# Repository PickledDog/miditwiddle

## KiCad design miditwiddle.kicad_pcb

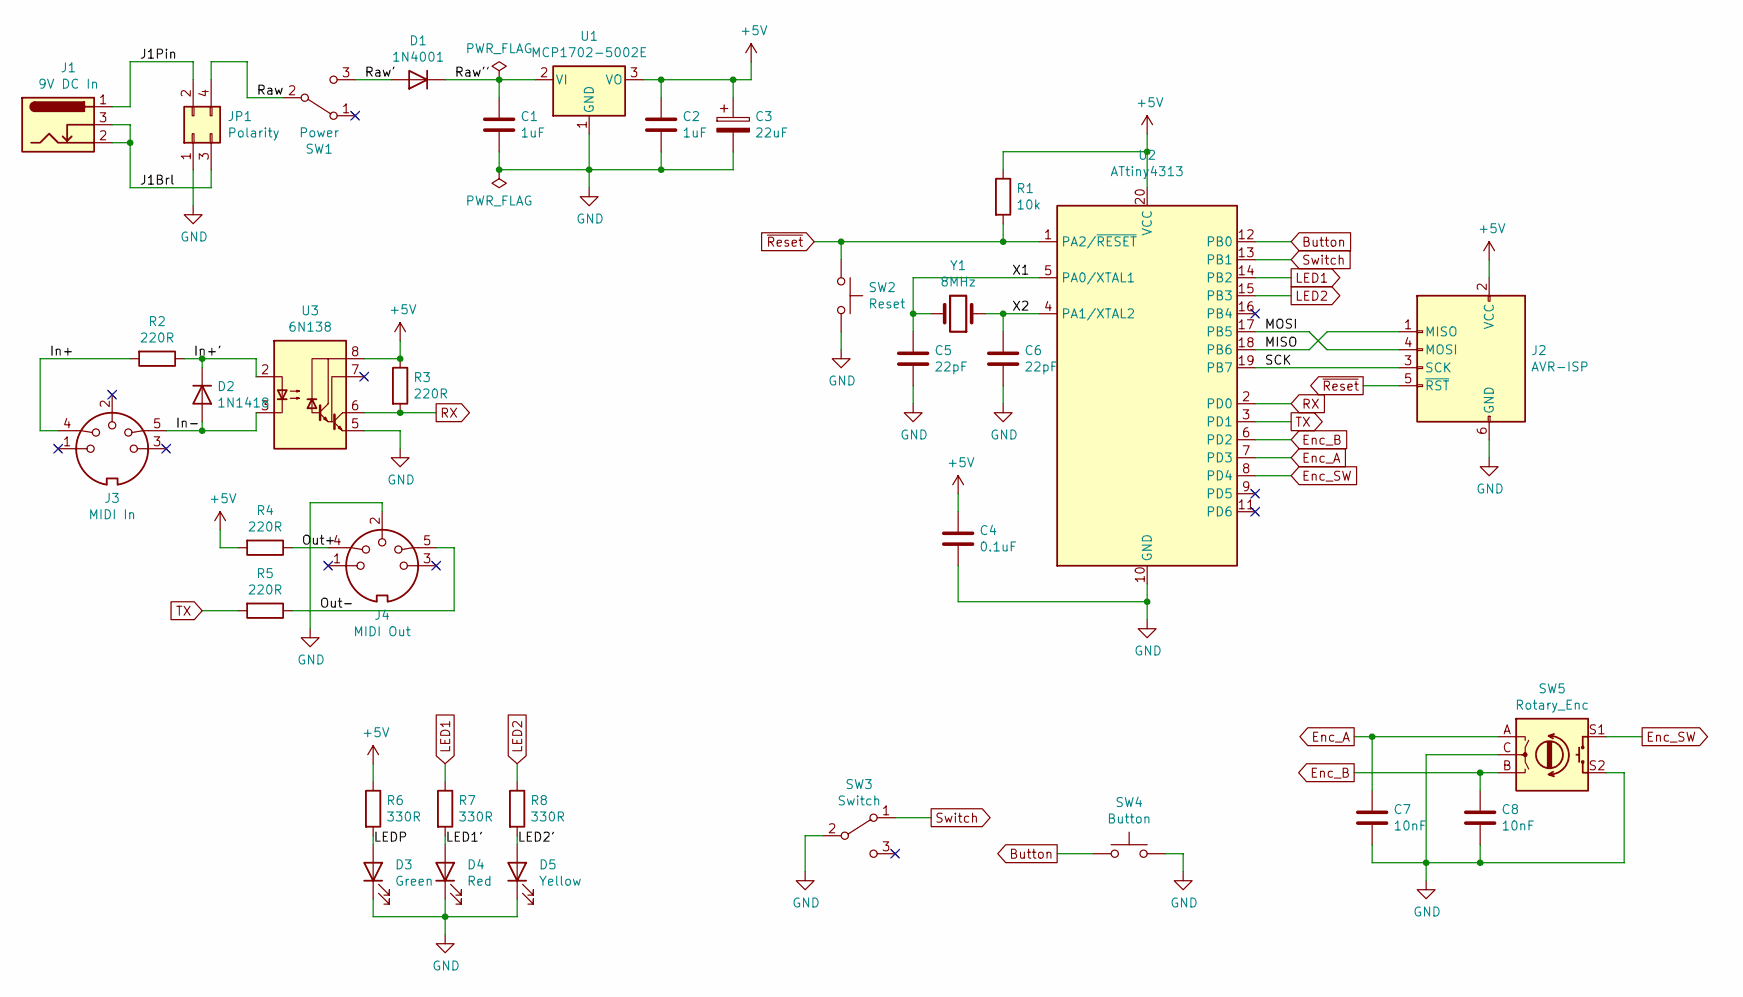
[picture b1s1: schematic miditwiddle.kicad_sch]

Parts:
C1, C2: 1uF; C_Disc_D3.0mm_W2.0mm_P2.50mm
C3: 22uF; CP_Radial_D5.0mm_P2.00mm
C4: 0.1uF; C_Disc_D3.0mm_W1.6mm_P2.50mm
C5, C6: 22pF; C_Disc_D3.0mm_W1.6mm_P2.50mm
C7, C8: 10nF; C_Disc_D3.0mm_W1.6mm_P2.50mm
D1: 1N4001; D_DO-41_SOD81_P10.16mm_Horizontal
D2: 1N1418; D_DO-35_SOD27_P7.62mm_Horizontal
D3: Green; LED_D3.0mm
D4: Red; LED_D3.0mm
D5: Yellow; LED_D3.0mm
J1: 9V DC In; BarrelJack_Horizontal
J2: AVR-ISP; IDC-Header_2x03_P2.54mm_Vertical
J3: MIDI In; DIN-5-180-Socket
J4: MIDI Out; DIN-5-180-Socket
JP1: Polarity; PinHeader_2x02_P2.54mm_Vertical
R1: 10k; R_Axial_DIN0207_L6.3mm_D2.5mm_P7.62mm_Horizontal
R2, R3, R4, R5: 220R; R_Axial_DIN0207_L6.3mm_D2.5mm_P7.62mm_Horizontal
R6, R7, R8: 330R; R_Axial_DIN0207_L6.3mm_D2.5mm_P7.62mm_Horizontal
SW1: Power; SW_CuK_OS102011MA1QN1_SPDT_Angled
SW2: Reset; SW_Tactile_SPST_Angled_PTS645Vx83-2LFS
SW3: Switch; SW_CuK_OS102011MA1QN1_SPDT_Angled
SW4: Button; SW_Tactile_SPST_Angled_PTS645Vx83-2LFS
SW5: Rotary_Enc; Rotary_Enc_Push
U1: MCP1702-5002E; TO-92
U2: ATtiny4313; DIP-20_W7.62mm_LongPads
U3: 6N138; DIP-8_W7.62mm_LongPads
Y1: 8MHz; Crystal_HC49-4H_Vertical

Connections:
+5V: C2.1, C3.1, C4.1, J2.2 (VCC), R1.1, R3.1, R4.2, R6.1, U1.3 (VO), U2.20 (VCC), U3.8 (VCC)
/In+: J3.4, R2.2
/In+': D2.1 (K), R2.1, U3.2 (C1)
/In-: D2.2 (A), J3.5, U3.3 (C2)
/J1Brl: J1.2, J1.3, JP1.3
/J1Pin: J1.1, JP1.2
/LED1': D4.2 (A), R7.2
/LED2': D5.2 (A), R8.2
/LEDP: D3.2 (A), R6.2
/MISO: J2.1 (MISO), U2.18 (PB6)
/MOSI: J2.4 (MOSI), U2.17 (PB5)
/Out+: J4.4, R4.1
/Out-: J4.5, R5.1
/Raw: JP1.4, SW1.2 (B)
/Raw': D1.2 (A), SW1.3 (C)
/Raw'': C1.1, D1.1 (K), U1.2 (VI)
/SCK: J2.3 (SCK), U2.19 (PB7)
/X1: C5.1, U2.5 (PA0/XTAL1), Y1.2
/X2: C6.1, U2.4 (PA1/XTAL2), Y1.1
Button: SW4.1, U2.12 (PB0)
Enc_A: C7.1, SW5.A, U2.7 (PD3)
Enc_B: C8.1, SW5.B, U2.6 (PD2)
Enc_SW: SW5.S1, U2.8 (PD4)
GND: C1.2, C2.2, C3.2, C4.2, C5.2, C6.2, C7.2, C8.2, D3.1 (K), D4.1 (K), D5.1 (K), J2.6 (GND), J4.2, J4.MH1, J4.MH2, JP1.1, SW2.2, SW3.2 (B), SW4.2, SW5.C, SW5.S2, U1.1 (GND), U2.10 (GND), U3.5 (GND)
LED1: R7.1, U2.14 (PB2)
LED2: R8.1, U2.15 (PB3)
RX: R3.2, U2.2 (PD0), U3.6 (VO2)
Switch: SW3.1 (A), U2.13 (PB1)
TX: R5.2, U2.3 (PD1)
~Reset: J2.5 (~RST), R1.2, SW2.1, U2.1 (PA2/~RESET)

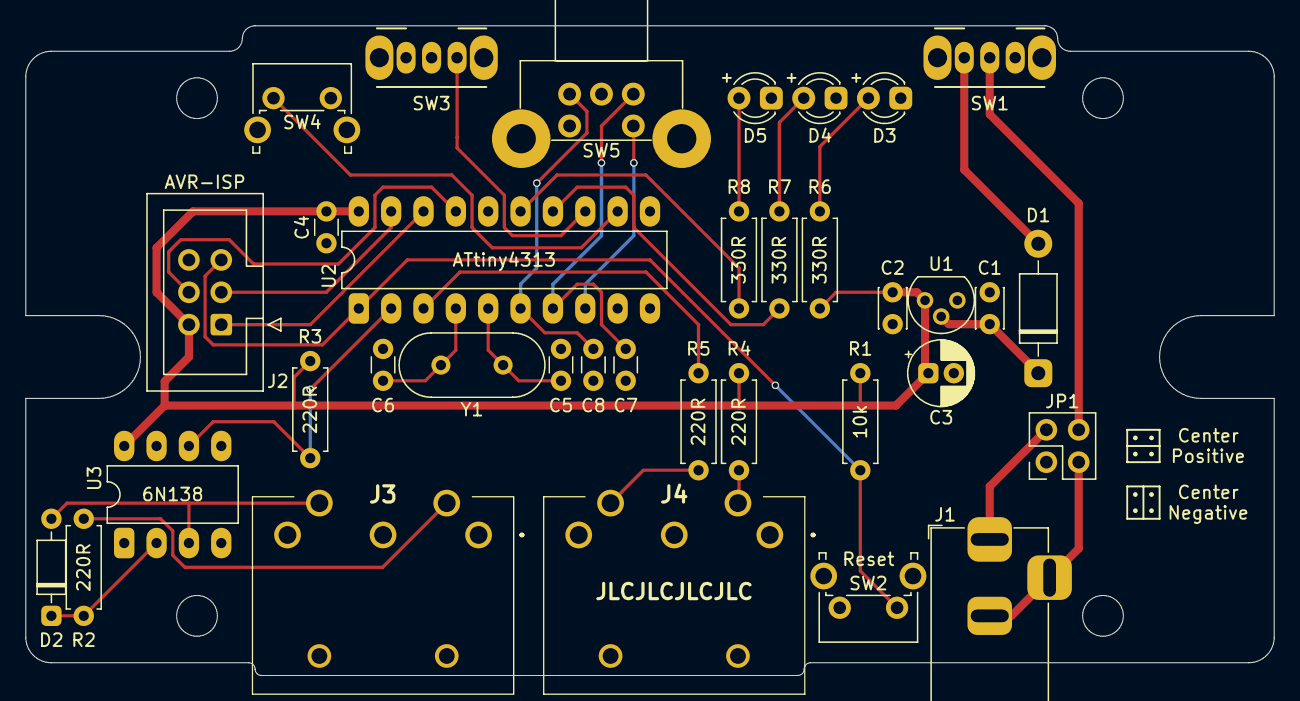
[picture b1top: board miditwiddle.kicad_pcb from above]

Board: 2 copper layers, 98.0 x 51.0 mm, 39 parts (0 on the bottom side), 30 nets.

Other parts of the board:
MH1, MH2, MH3, MH4: 3.2mm; MountingHole_3.2mm_M3

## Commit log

2021-04-05 Initial commit of miditwiddle/PD201
2023-08-24 Migrate project to KiCad 6

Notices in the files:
miditwiddle.kicad_pcb:
(C) 2021
